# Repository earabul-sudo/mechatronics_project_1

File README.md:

# mechatronics_project_1
Strip Board Schematics/Board View to utilise a 2 axis gantry table

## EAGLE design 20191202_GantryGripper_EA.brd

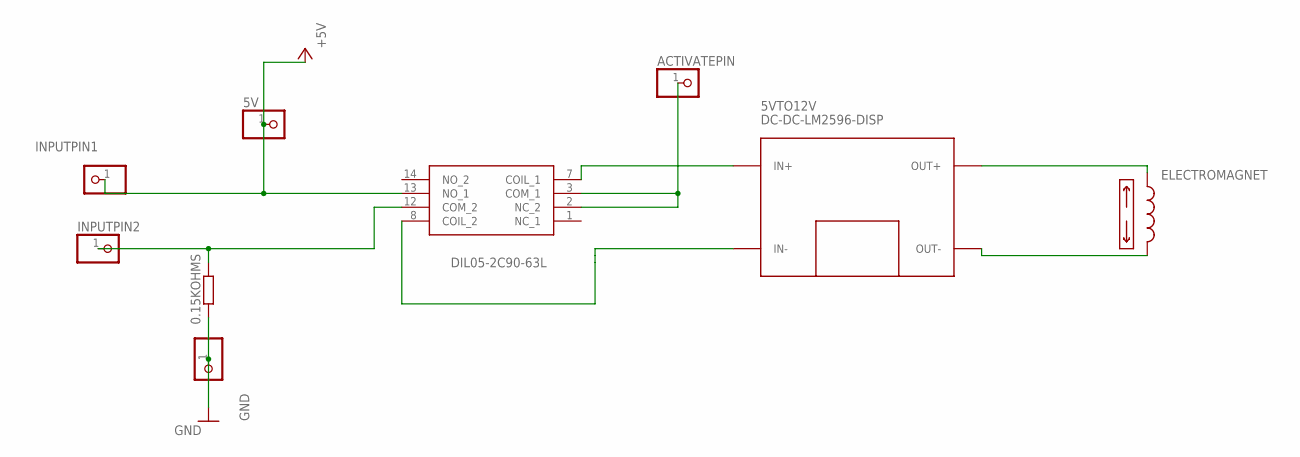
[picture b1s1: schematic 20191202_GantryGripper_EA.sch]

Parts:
0.15KOHMS: R-EU_0204/2V; 0204V
5V: PINHD-1X1; 1X01
5VTO12V: DC-DC-LM2596-DISP
ACTIVATEPIN: PINHD-1X1; 1X01
ELECTROMAGNET: SOLENOID; 1X02
GND: PINHD-1X1; 1X01
INPUTPIN1, INPUTPIN2: PINHD-1X1; 1X01
K1: DIL05-2C90-63L; DIL052C9063L

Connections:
+5V: 5V.1, INPUTPIN1.1, K1.13 (NO_1)
GND: 0.15KOHMS.1, GND.1
unnamed: 5VTO12V.IN+, K1.7 (COIL_1)
unnamed: 5VTO12V.IN-, K1.8 (COIL_2)
unnamed: ACTIVATEPIN.1, K1.2 (NC_2), K1.3 (COM_1)
unnamed: 0.15KOHMS.2, INPUTPIN2.1, K1.12 (COM_2)
unnamed: 5VTO12V.OUT+, ELECTROMAGNET.1
unnamed: 5VTO12V.OUT-, ELECTROMAGNET.2

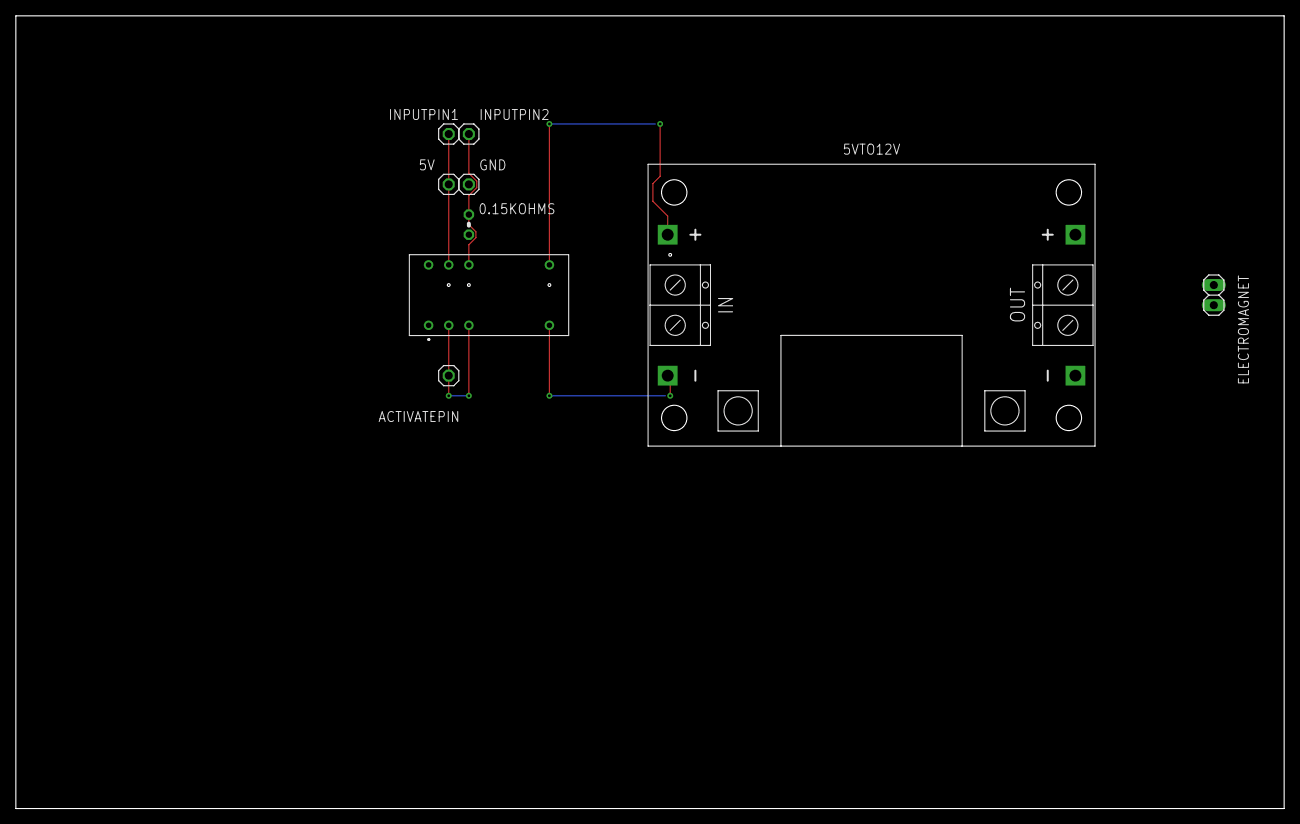
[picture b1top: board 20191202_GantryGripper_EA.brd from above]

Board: 2 copper layers, 160.0 x 100.0 mm, 9 parts (0 on the bottom side), 8 nets.

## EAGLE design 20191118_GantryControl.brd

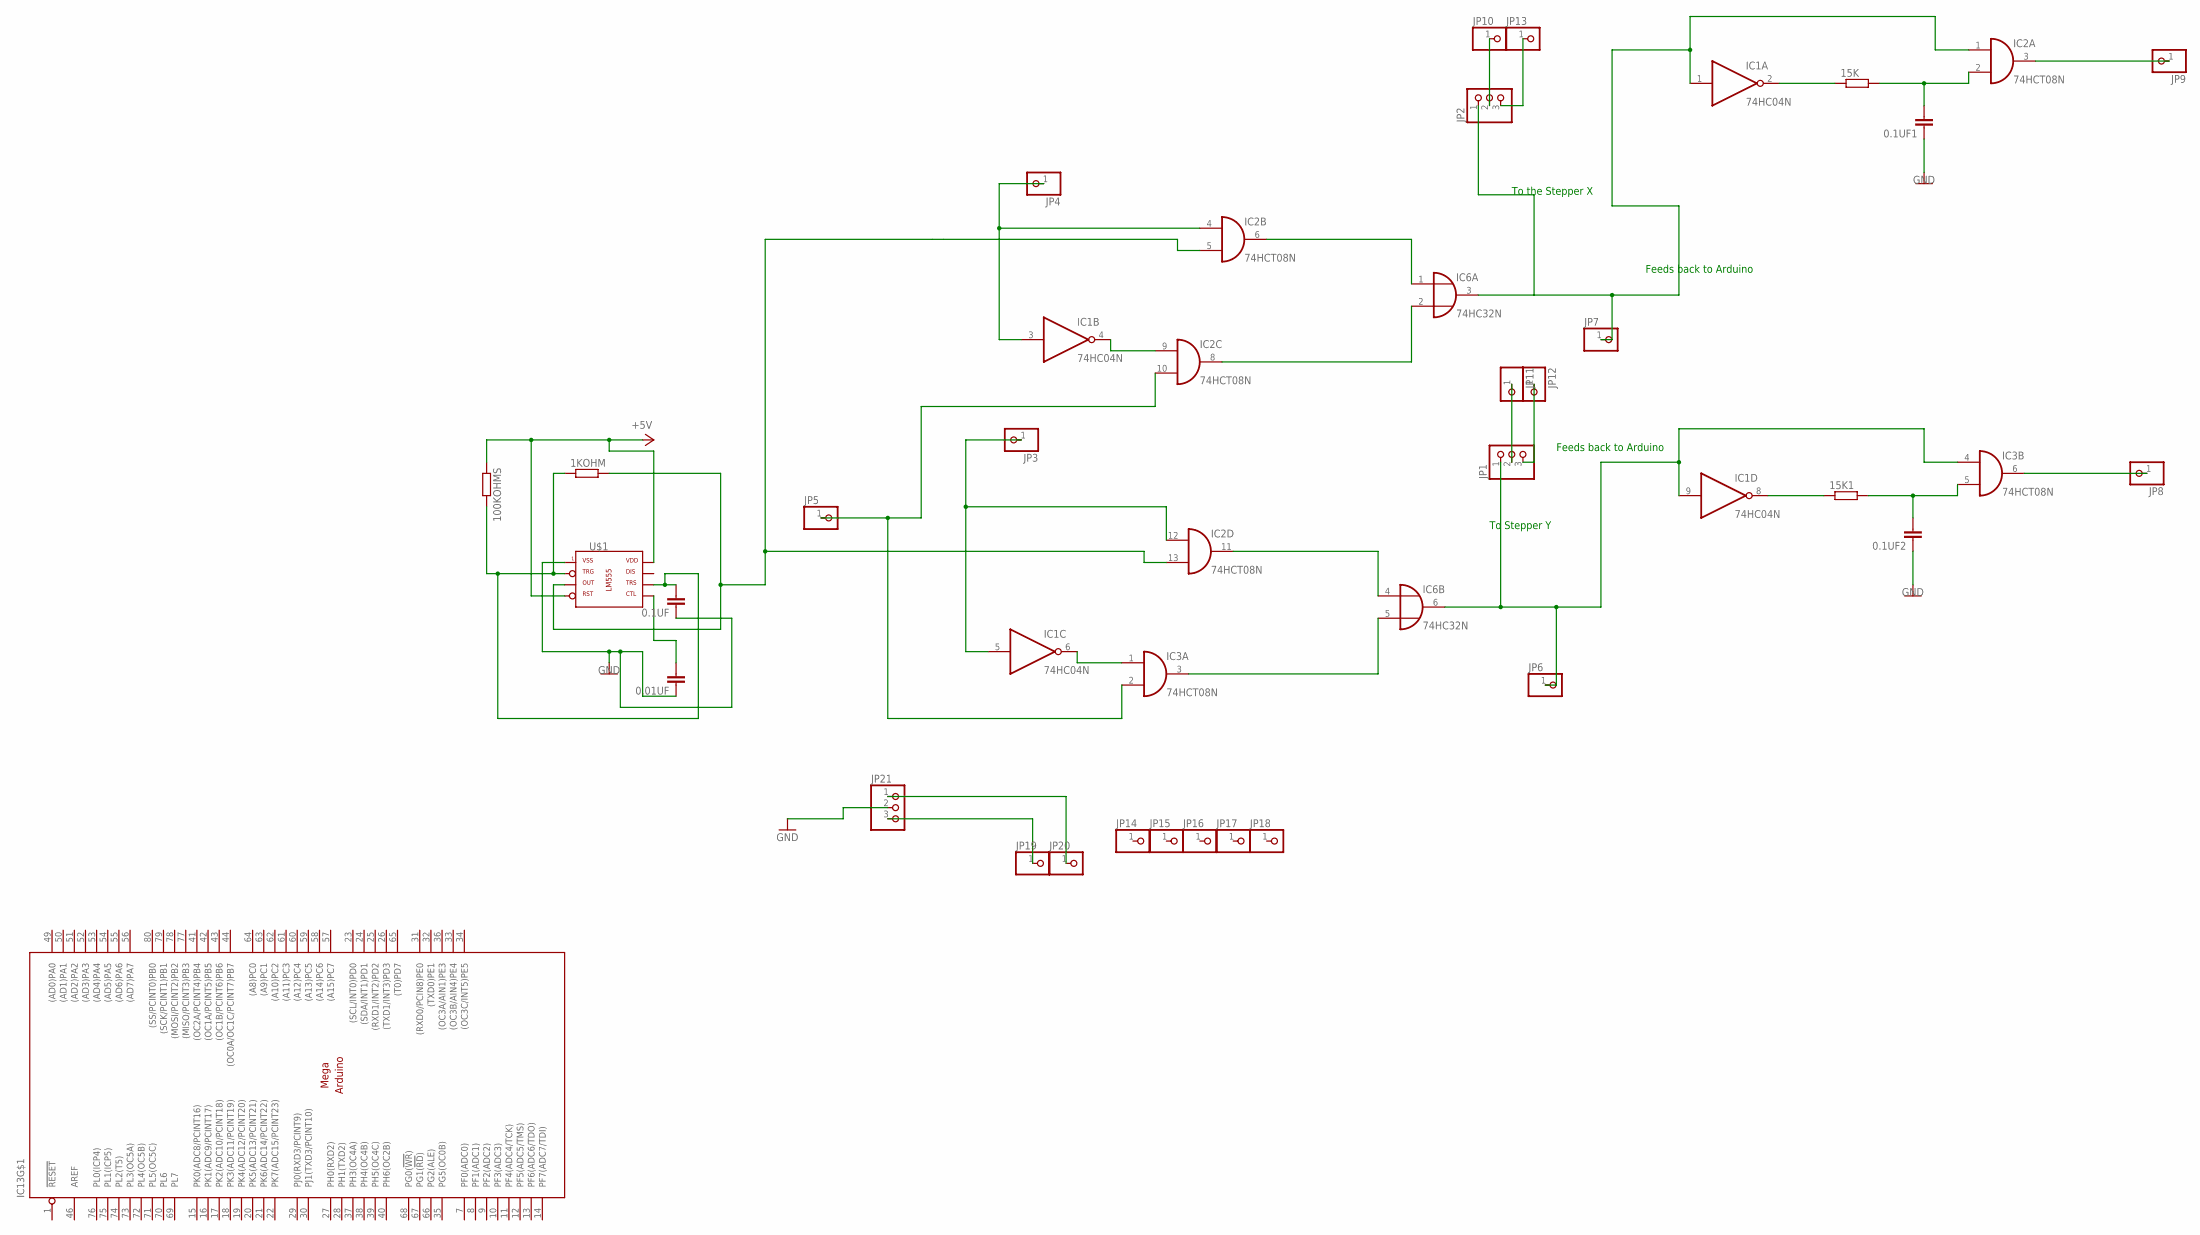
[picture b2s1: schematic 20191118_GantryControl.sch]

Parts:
0.1UF, 0.1UF1, 0.1UF2: C-EU075-032X103; C075-032X103
0.01UF: C-EU102-064X133; C102-064X133
1KOHM: R-EU_0207/12; 0207/12
15K, 15K1, 100KOHMS: R-EU_0207/10; 0207/10
IC1: 74HC04N; DIL14
IC2, IC3: 74HCT08N; DIL14
IC6: 74HC32N; DIL14
IC13: MEGAARDUINO_20; MEGA_ARDUINO
JP1, JP2, JP21: PINHD-1X3; 1X03
JP3, JP4, JP5, JP6, JP7, JP8, JP9, JP10, JP11, JP12, JP13, JP14, JP15, JP16, JP17, JP18, JP19, JP20: PINHD-1X1; 1X01
U$1: -LM555; DIL08

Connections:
+3V3: IC13.2 (+3V3)
+5V: 100KOHMS.1, IC13.3 (+5V), IC13.47 (+5V), IC13.48 (+5V), U$1.4 (RES), U$1.8 (VCC)
+VIN: IC13.6 (+VIN)
GND: 0.01UF.1, 0.1UF.1, 0.1UF1.1, 0.1UF2.1, IC1.7 (GND), IC2.7 (GND), IC3.7 (GND), IC6.7 (GND), IC13.4 (GND), IC13.5 (GND), IC13.45 (GND), IC13.81 (GND), IC13.82 (GND), JP21.2, U$1.1 (GND)
unnamed: 1KOHM.2, IC2.5 (I1), IC2.13 (I1), U$1.3 (OUT)
unnamed: 0.1UF.2, 1KOHM.1, 100KOHMS.2, U$1.2 (TRG), U$1.6 (TRS)
unnamed: 0.01UF.2, U$1.5 (CTL)
unnamed: 15K.1, IC1.2 (O)
unnamed: IC1.1 (I), IC2.1 (I0), IC6.3 (O), JP2.1, JP7.1
unnamed: 0.1UF1.2, 15K.2, IC2.2 (I1)
unnamed: IC3.6 (O), JP8.1
unnamed: IC1.3 (I), IC2.4 (I0), JP4.1
unnamed: IC2.3 (O), JP9.1
unnamed: IC2.10 (I1), IC3.2 (I1), JP5.1
unnamed: IC1.4 (O), IC2.9 (I0)
unnamed: IC2.8 (O), IC6.2 (I1)
unnamed: JP1.2, JP11.1
unnamed: IC2.6 (O), IC6.1 (I0)
unnamed: IC1.5 (I), IC2.12 (I0), JP3.1
unnamed: JP1.3, JP12.1
unnamed: JP2.2, JP10.1
unnamed: IC1.6 (O), IC3.1 (I0)
unnamed: IC3.3 (O), IC6.5 (I1)
unnamed: IC2.11 (O), IC6.4 (I0)
unnamed: IC1.9 (I), IC3.4 (I0), IC6.6 (O), JP1.1, JP6.1
unnamed: 15K1.1, IC1.8 (O)
unnamed: 0.1UF2.2, 15K1.2, IC3.5 (I1)
unnamed: JP2.3, JP13.1
unnamed: JP19.1, JP21.3
unnamed: JP20.1, JP21.1
VCC: IC1.14 (VCC), IC2.14 (VCC), IC3.14 (VCC), IC6.14 (VCC)

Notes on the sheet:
To the Stepper X
Feeds back to Arduino
To Stepper Y

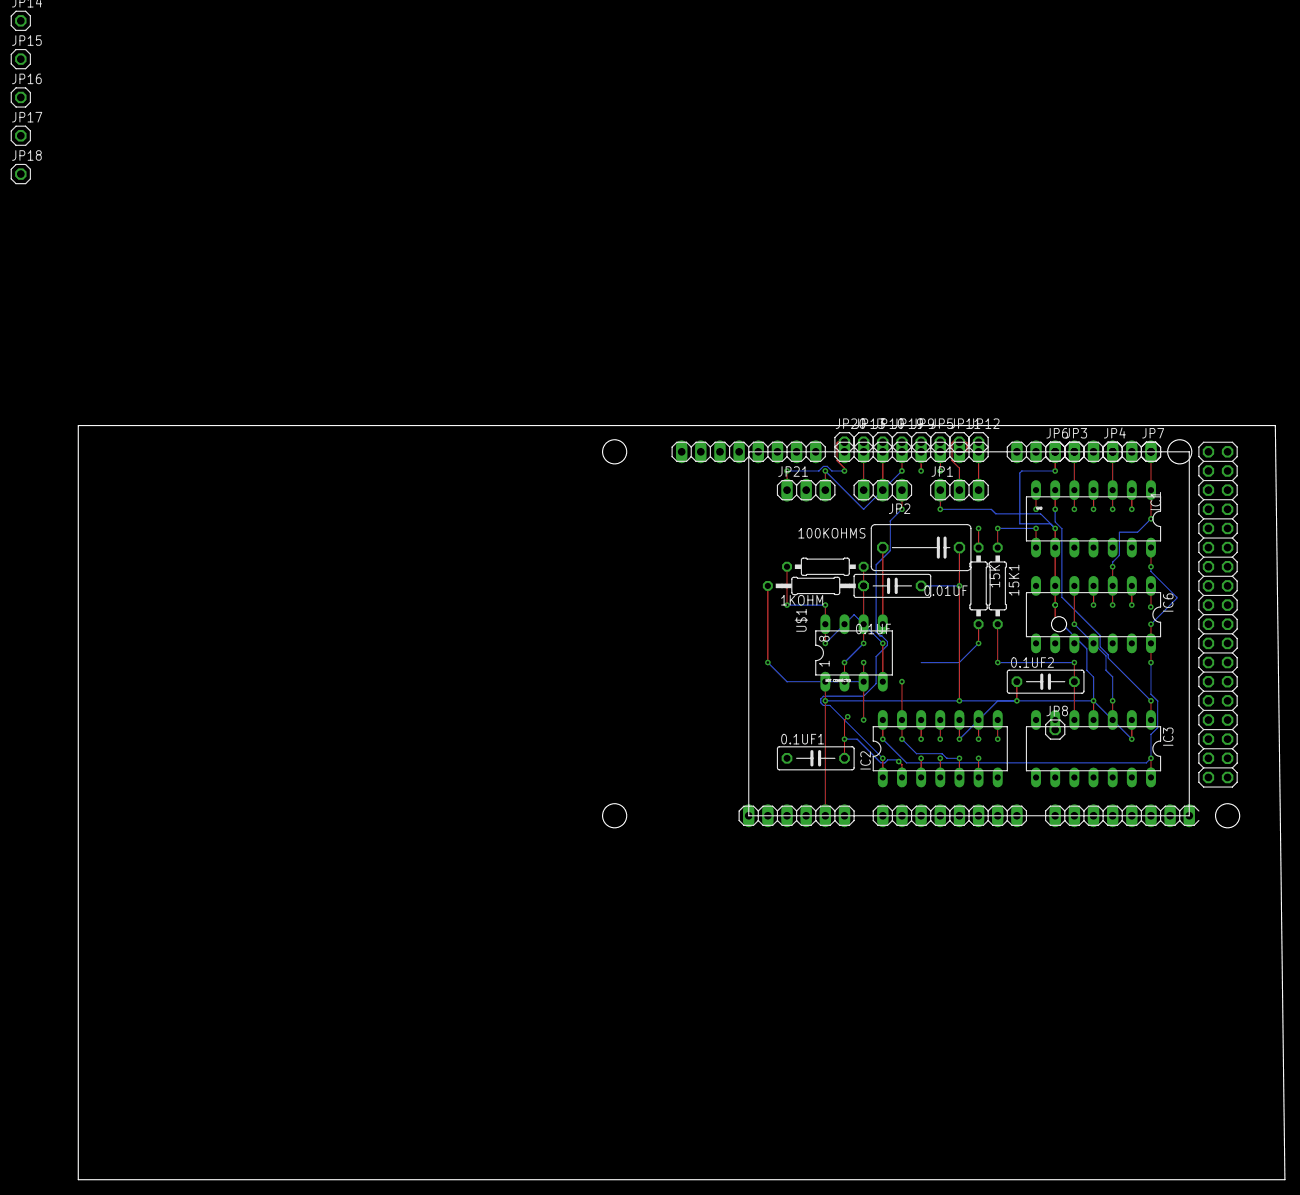
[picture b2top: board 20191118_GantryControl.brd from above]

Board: 2 copper layers, 160.0 x 100.0 mm, 35 parts (0 on the bottom side), 29 nets.

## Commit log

2020-06-28 Create Gripper

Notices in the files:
parts and their libraries:
diy-modules: Released under the Creative Commons Attribution 4.0 International License: http://creativecommons.org/licenses/by/4.0
